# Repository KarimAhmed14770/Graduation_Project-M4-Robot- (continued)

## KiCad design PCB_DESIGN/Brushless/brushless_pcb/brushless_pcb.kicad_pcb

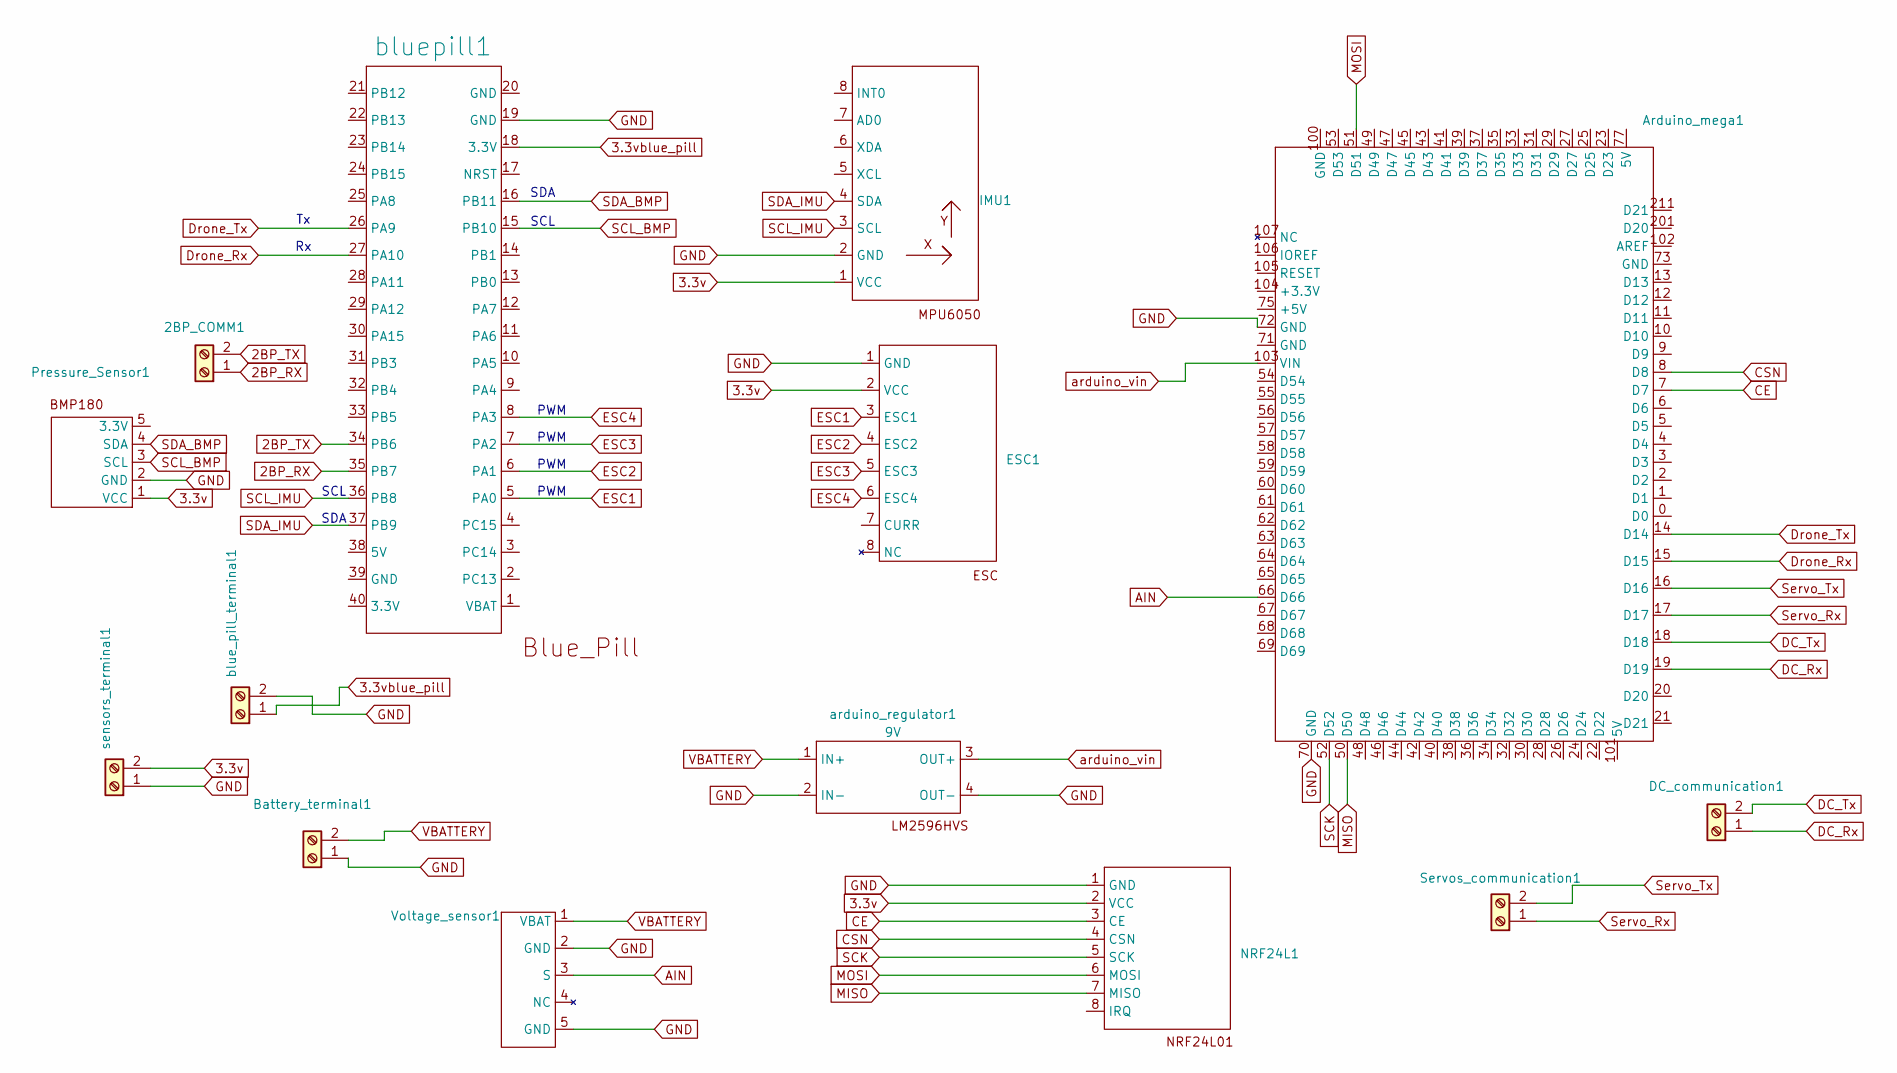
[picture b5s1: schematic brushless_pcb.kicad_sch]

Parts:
2BP_COMM1: TerminalBlock_Altech_AK300-2_P5.00mm
Arduino_mega1: mega_reverse
Battery_terminal1: battery
DC_communication1: TerminalBlock_Altech_AK300-2_P5.00mm
ESC1: TerminalBlock_bornier-8_P5.08mm
IMU1: MPU6050
NRF24L1: NRF24L1
Pressure_Sensor1: BMP180
Servos_communication1: TerminalBlock_Altech_AK300-2_P5.00mm
Voltage_sensor1: Voltage_sensor
arduino_regulator1: 9V; LM2596HVS
blue_pill_terminal1: Screw_Terminal_01x02; TerminalBlock_Altech_AK300-2_P5.00mm
bluepill1: blue_pill
sensors_terminal1: Screw_Terminal_01x02; TerminalBlock_Altech_AK300-2_P5.00mm

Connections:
2BP_RX: 2BP_COMM1.1, bluepill1.35 (PB7)
2BP_TX: 2BP_COMM1.2, bluepill1.34 (PB6)
3.3v: ESC1.2 (VCC), IMU1.1 (VCC), NRF24L1.2 (VCC), Pressure_Sensor1.1 (VCC), sensors_terminal1.2
3.3vblue_pill: blue_pill_terminal1.1, bluepill1.18 (3.3V)
AIN: Arduino_mega1.66 (D66), Voltage_sensor1.3 (S)
CE: Arduino_mega1.7 (D7), NRF24L1.3 (CE)
CSN: Arduino_mega1.8 (D8), NRF24L1.4 (CSN)
DC_Rx: Arduino_mega1.19 (D19), DC_communication1.1
DC_Tx: Arduino_mega1.18 (D18), DC_communication1.2
Drone_Rx: Arduino_mega1.15 (D15), bluepill1.27 (PA10)
Drone_Tx: Arduino_mega1.14 (D14), bluepill1.26 (PA9)
ESC1: ESC1.3 (ESC1), bluepill1.5 (PA0)
ESC2: ESC1.4 (ESC2), bluepill1.6 (PA1)
ESC3: ESC1.5 (ESC3), bluepill1.7 (PA2)
ESC4: ESC1.6 (ESC4), bluepill1.8 (PA3)
GND: Arduino_mega1.70 (GND), Arduino_mega1.72 (GND), Battery_terminal1.1, ESC1.1 (GND), IMU1.2 (GND), NRF24L1.1 (GND), Pressure_Sensor1.2 (GND), Voltage_sensor1.2 (GND), Voltage_sensor1.5 (GND), arduino_regulator1.2 (IN-), arduino_regulator1.4 (OUT-), blue_pill_terminal1.2, bluepill1.19 (GND), sensors_terminal1.1
MISO: Arduino_mega1.50 (D50), NRF24L1.7 (MISO)
MOSI: Arduino_mega1.51 (D51), NRF24L1.6 (MOSI)
SCK: Arduino_mega1.52 (D52), NRF24L1.5 (SCK)
SCL_BMP: Pressure_Sensor1.3 (SCL), bluepill1.15 (PB10)
SCL_IMU: IMU1.3 (SCL), bluepill1.36 (PB8)
SDA_BMP: Pressure_Sensor1.4 (SDA), bluepill1.16 (PB11)
SDA_IMU: IMU1.4 (SDA), bluepill1.37 (PB9)
Servo_Rx: Arduino_mega1.17 (D17), Servos_communication1.1
Servo_Tx: Arduino_mega1.16 (D16), Servos_communication1.2
VBATTERY: Battery_terminal1.2, Voltage_sensor1.1 (VBAT), arduino_regulator1.1 (IN+)
arduino_vin: Arduino_mega1.103 (VIN), arduino_regulator1.3 (OUT+)

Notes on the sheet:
PWM
SDA
SCL
SCL

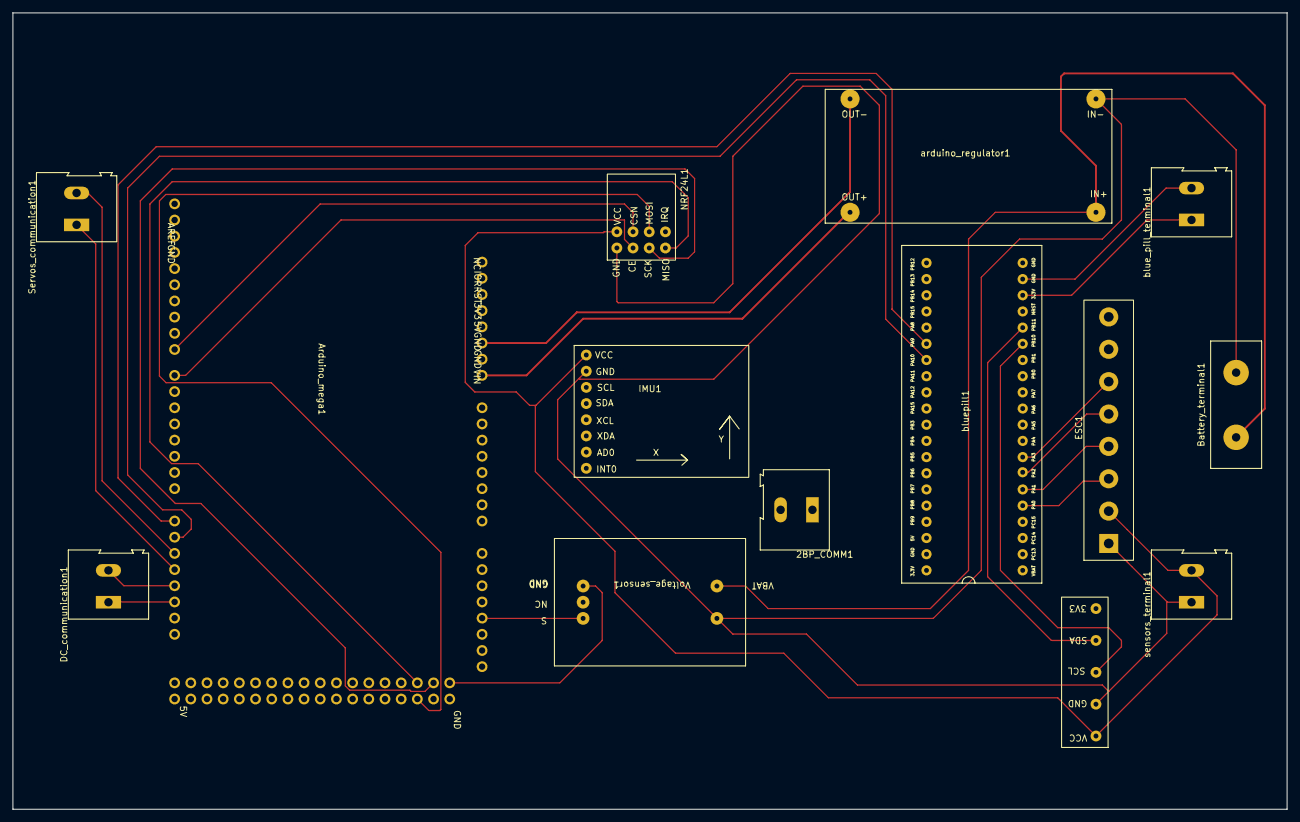
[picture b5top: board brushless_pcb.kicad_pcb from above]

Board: 2 copper layers, 200.0 x 125.0 mm, 14 parts (0 on the bottom side), 27 nets.

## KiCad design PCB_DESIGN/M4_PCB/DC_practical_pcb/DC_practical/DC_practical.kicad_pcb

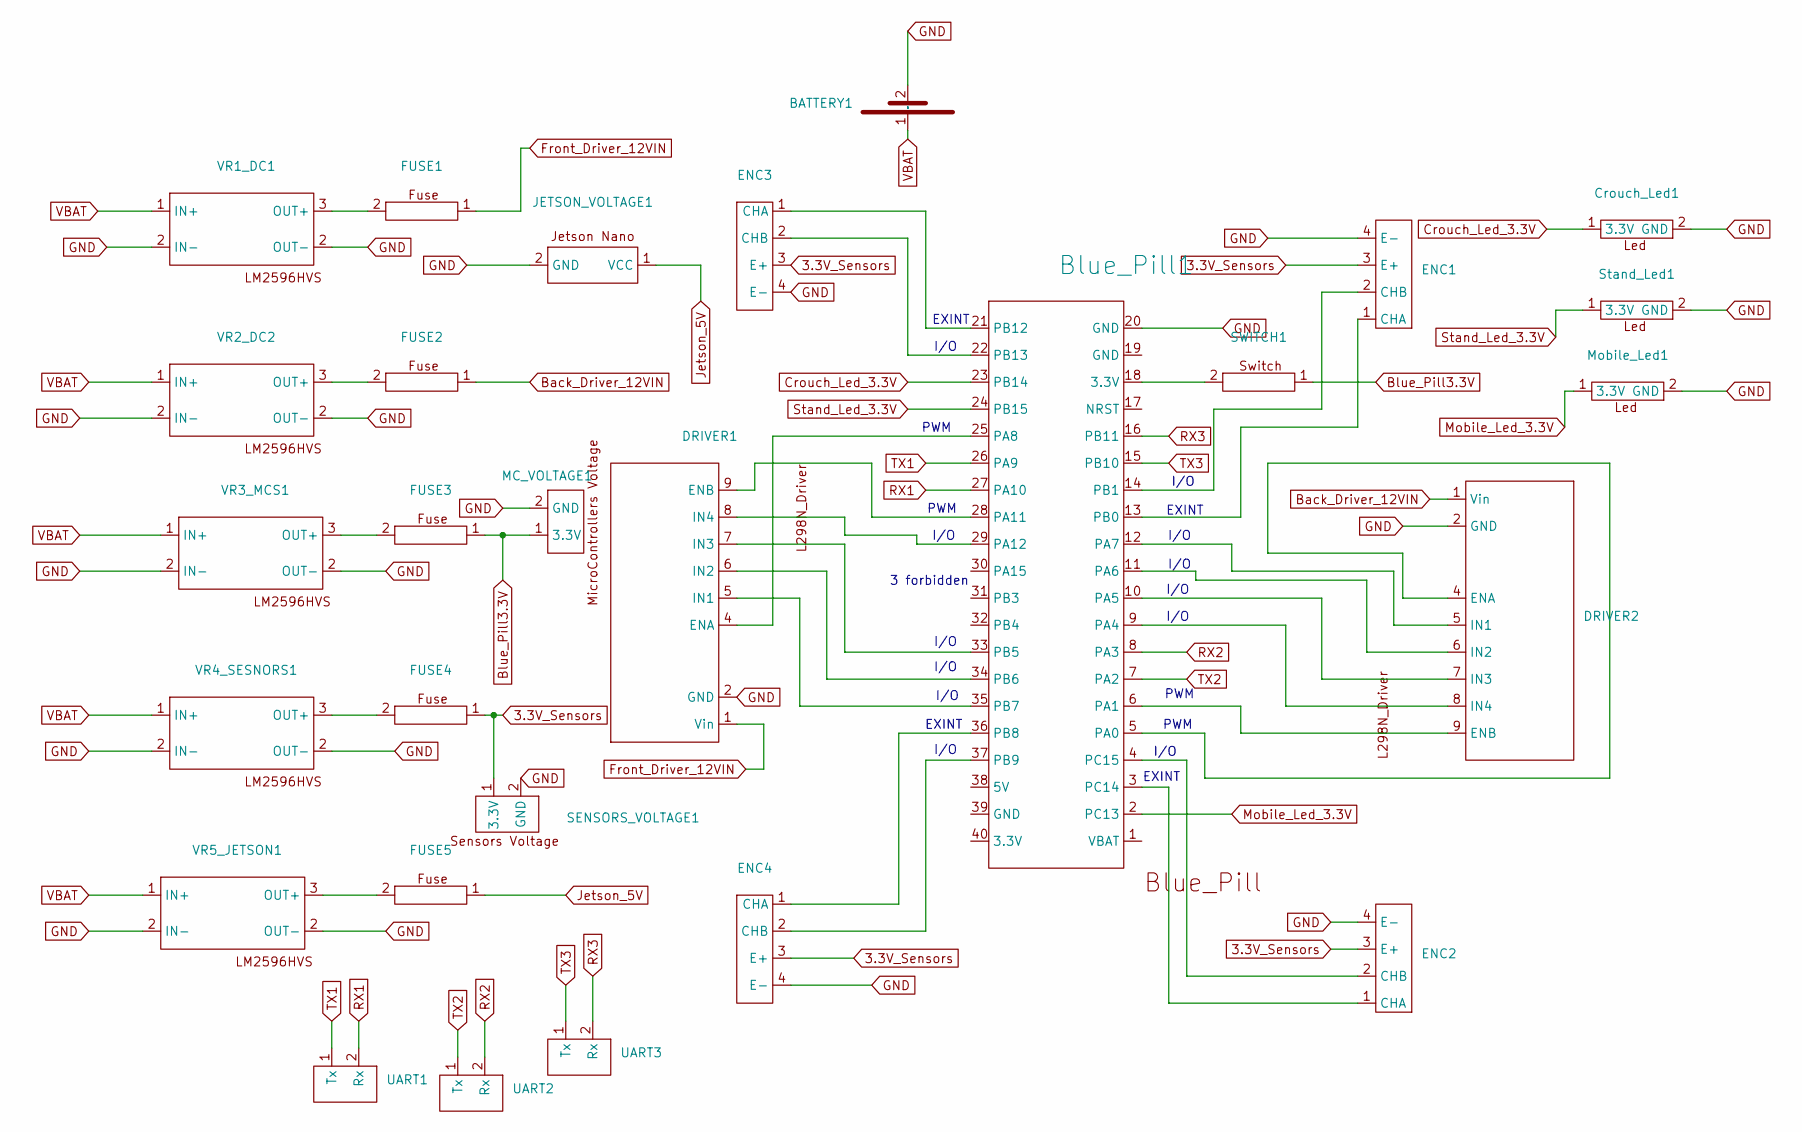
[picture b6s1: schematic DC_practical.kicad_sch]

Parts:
BATTERY1: battery
Blue_Pill1: blue_pill
Crouch_Led1: LED
DRIVER1, DRIVER2: L298N
ENC1, ENC2, ENC3, ENC4: Encoder
FUSE1, FUSE2, FUSE3, FUSE4, FUSE5: Fuse_Holder
JETSON_VOLTAGE1: Jetson_Voltage
MC_VOLTAGE1: Microcontrollers
Mobile_Led1: LED
SENSORS_VOLTAGE1: sensors
SWITCH1: switch
Stand_Led1: LED
UART1, UART2, UART3: communication
VR1_DC1, VR2_DC2, VR3_MCS1, VR4_SESNORS1, VR5_JETSON1: LM2596HVS

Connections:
3.3V_Sensors: ENC1.3 (E+), ENC2.3 (E+), ENC3.3 (E+), ENC4.3 (E+), FUSE4.1, SENSORS_VOLTAGE1.1 (3.3V)
Back_Driver_12VIN: DRIVER2.1 (Vin), FUSE2.1
Blue_Pill3.3V: FUSE3.1, MC_VOLTAGE1.1 (3.3V), SWITCH1.1
Crouch_Led_3.3V: Blue_Pill1.23 (PB14), Crouch_Led1.1 (3.3V)
Front_Driver_12VIN: DRIVER1.1 (Vin), FUSE1.1
GND: BATTERY1.2 (GND), Blue_Pill1.20 (GND), Crouch_Led1.2 (GND), DRIVER1.2 (GND), DRIVER2.2 (GND), ENC1.4 (E-), ENC2.4 (E-), ENC3.4 (E-), ENC4.4 (E-), JETSON_VOLTAGE1.2 (GND), MC_VOLTAGE1.2 (GND), Mobile_Led1.2 (GND), SENSORS_VOLTAGE1.2 (GND), Stand_Led1.2 (GND), VR1_DC1.2 (IN-), VR2_DC2.2 (OUT-), VR3_MCS1.2 (IN-), VR4_SESNORS1.2 (OUT-), VR5_JETSON1.2 (OUT-)
Jetson_5V: FUSE5.1, JETSON_VOLTAGE1.1 (VCC)
Mobile_Led_3.3V: Blue_Pill1.2 (PC13), Mobile_Led1.1 (3.3V)
unnamed: Blue_Pill1.18 (3.3V), SWITCH1.2
unnamed: Blue_Pill1.5 (PA0), DRIVER2.4 (ENA)
unnamed: Blue_Pill1.6 (PA1), DRIVER2.9 (ENB)
unnamed: Blue_Pill1.9 (PA4), DRIVER2.8 (IN4)
unnamed: Blue_Pill1.10 (PA5), DRIVER2.7 (IN3)
unnamed: Blue_Pill1.11 (PA6), DRIVER2.6 (IN2)
unnamed: Blue_Pill1.12 (PA7), DRIVER2.5 (IN1)
unnamed: Blue_Pill1.25 (PA8), DRIVER1.4 (ENA)
unnamed: Blue_Pill1.28 (PA11), DRIVER1.9 (ENB)
unnamed: Blue_Pill1.29 (PA12), DRIVER1.8 (IN4)
unnamed: Blue_Pill1.13 (PB0), ENC1.1 (CHA)
unnamed: Blue_Pill1.14 (PB1), ENC1.2 (CHB)
unnamed: Blue_Pill1.33 (PB5), DRIVER1.7 (IN3)
unnamed: Blue_Pill1.34 (PB6), DRIVER1.6 (IN2)
unnamed: Blue_Pill1.35 (PB7), DRIVER1.5 (IN1)
unnamed: Blue_Pill1.36 (PB8), ENC4.1 (CHA)
unnamed: Blue_Pill1.37 (PB9), ENC4.2 (CHB)
unnamed: Blue_Pill1.21 (PB12), ENC3.1 (CHA)
unnamed: Blue_Pill1.22 (PB13), ENC3.2 (CHB)
unnamed: Blue_Pill1.3 (PC14), ENC2.1 (CHA)
unnamed: Blue_Pill1.4 (PC15), ENC2.2 (CHB)
unnamed: FUSE1.2, VR1_DC1.3 (OUT+)
unnamed: FUSE2.2, VR2_DC2.3 (OUT+)
unnamed: FUSE3.2, VR3_MCS1.3 (OUT+)
unnamed: FUSE4.2, VR4_SESNORS1.3 (OUT+)
unnamed: FUSE5.2, VR5_JETSON1.3 (OUT+)
RX1: Blue_Pill1.27 (PA10), UART1.2 (Rx)
RX2: Blue_Pill1.8 (PA3), UART2.2 (Rx)
RX3: Blue_Pill1.16 (PB11), UART3.2 (Rx)
Stand_Led_3.3V: Blue_Pill1.24 (PB15), Stand_Led1.1 (3.3V)
TX1: Blue_Pill1.26 (PA9), UART1.1 (Tx)
TX2: Blue_Pill1.7 (PA2), UART2.1 (Tx)
TX3: Blue_Pill1.15 (PB10), UART3.1 (Tx)
VBAT: BATTERY1.1 (VDD), VR1_DC1.1 (IN+), VR2_DC2.1 (IN+), VR3_MCS1.1 (IN+), VR4_SESNORS1.1 (IN+), VR5_JETSON1.1 (IN+)

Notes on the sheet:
I/O
PWM
EXINT
3 forbidden

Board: 2 copper layers, 28 parts (0 on the bottom side), 42 nets, no tracks yet.

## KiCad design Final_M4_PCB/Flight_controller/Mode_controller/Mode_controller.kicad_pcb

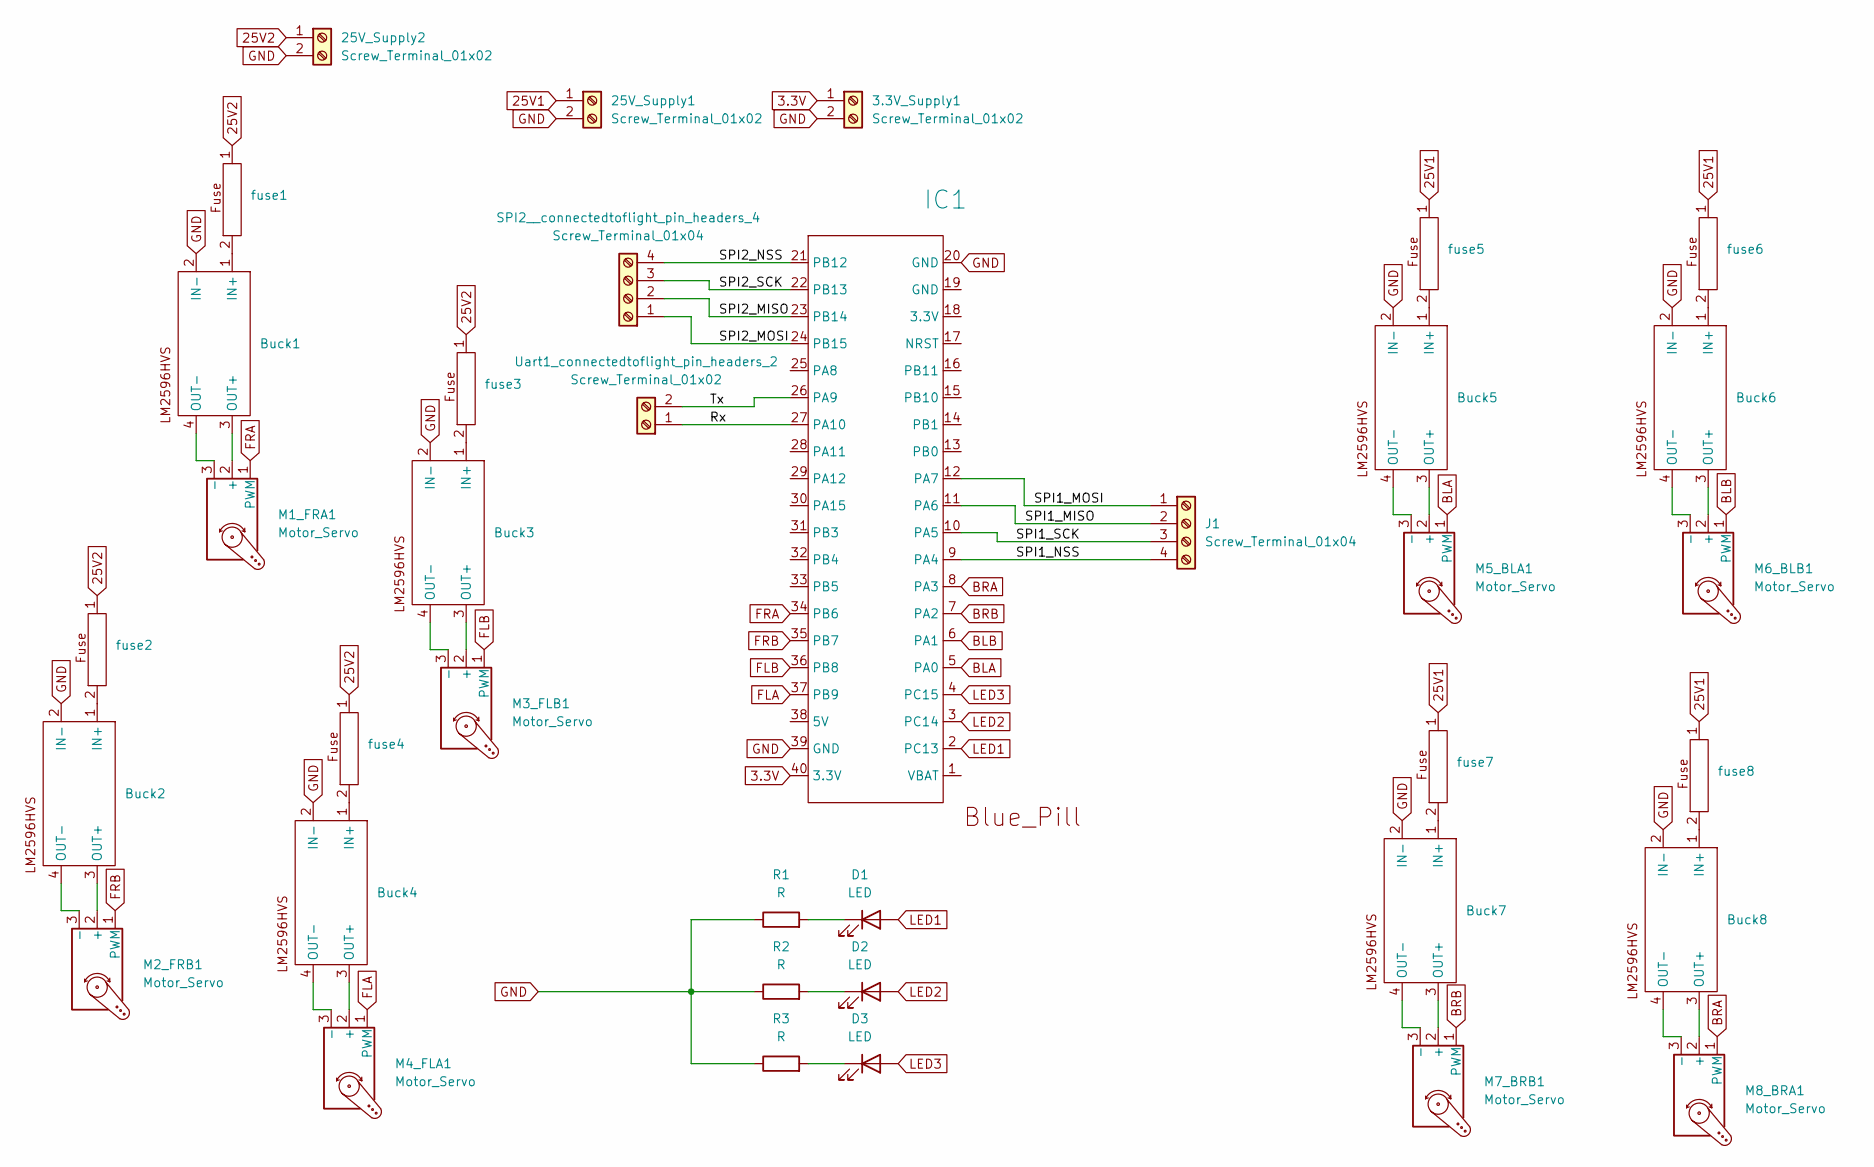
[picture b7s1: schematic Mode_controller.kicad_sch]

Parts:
3.3V_Supply1: Screw_Terminal_01x02; PinHeader_1x02_P2.54mm_Vertical
25V_Supply1, 25V_Supply2: Screw_Terminal_01x02; TerminalBlock_Dinkle_DT-55-B01X-02_P10.00mm
Buck1, Buck2, Buck3, Buck4, Buck5, Buck6, Buck7, Buck8: LM2596HVS
D1, D2, D3: LED; LED_D3.0mm
IC1: blue_pill
J1: Screw_Terminal_01x04; PinHeader_1x04_P2.54mm_Vertical
M1_FRA1, M2_FRB1, M3_FLB1, M4_FLA1, M5_BLA1, M6_BLB1, M7_BRB1, M8_BRA1: Motor_Servo; Servo
R1, R2, R3: R; R_Axial_DIN0204_L3.6mm_D1.6mm_P2.54mm_Vertical
SPI2__connectedtoflight_pin_headers_4: Screw_Terminal_01x04; PinHeader_1x04_P2.54mm_Vertical
Uart1_connectedtoflight_pin_headers_2: Screw_Terminal_01x02; PinHeader_1x02_P2.54mm_Vertical
fuse1, fuse2, fuse3, fuse4, fuse5, fuse6, fuse7, fuse8: Fuse_Holder

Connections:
3.3V: 3.3V_Supply1.1, IC1.40 (3.3V)
25V1: 25V_Supply1.1, fuse5.1, fuse6.1, fuse7.1, fuse8.1
25V2: 25V_Supply2.1, fuse1.1, fuse2.1, fuse3.1, fuse4.1
/Rx: IC1.27 (PA10), Uart1_connectedtoflight_pin_headers_2.1
/SPI1_MISO: IC1.11 (PA6), J1.2
/SPI1_MOSI: IC1.12 (PA7), J1.1
/SPI1_NSS: IC1.9 (PA4), J1.4
/SPI1_SCK: IC1.10 (PA5), J1.3
/SPI2_MISO: IC1.23 (PB14), SPI2__connectedtoflight_pin_headers_4.2
/SPI2_MOSI: IC1.24 (PB15), SPI2__connectedtoflight_pin_headers_4.1
/SPI2_NSS: IC1.21 (PB12), SPI2__connectedtoflight_pin_headers_4.4
/SPI2_SCK: IC1.22 (PB13), SPI2__connectedtoflight_pin_headers_4.3
/Tx: IC1.26 (PA9), Uart1_connectedtoflight_pin_headers_2.2
BLA: IC1.5 (PA0), M5_BLA1.1 (PWM)
BLB: IC1.6 (PA1), M6_BLB1.1 (PWM)
BRA: IC1.8 (PA3), M8_BRA1.1 (PWM)
BRB: IC1.7 (PA2), M7_BRB1.1 (PWM)
FLA: IC1.37 (PB9), M4_FLA1.1 (PWM)
FLB: IC1.36 (PB8), M3_FLB1.1 (PWM)
FRA: IC1.34 (PB6), M1_FRA1.1 (PWM)
FRB: IC1.35 (PB7), M2_FRB1.1 (PWM)
GND: 3.3V_Supply1.2, 25V_Supply1.2, 25V_Supply2.2, Buck1.2 (IN-), Buck2.2 (IN-), Buck3.2 (IN-), Buck4.2 (IN-), Buck5.2 (IN-), Buck6.2 (IN-), Buck7.2 (IN-), Buck8.2 (IN-), IC1.20 (GND), IC1.39 (GND), R1.1, R2.1, R3.1
LED1: D1.2 (A), IC1.2 (PC13)
LED2: D2.2 (A), IC1.3 (PC14)
LED3: D3.2 (A), IC1.4 (PC15)
unnamed: Buck1.1 (IN+), fuse1.2
unnamed: Buck1.3 (OUT+), M1_FRA1.2 (+)
unnamed: Buck1.4 (OUT-), M1_FRA1.3 (-)
unnamed: Buck2.1 (IN+), fuse2.2
unnamed: Buck2.3 (OUT+), M2_FRB1.2 (+)
unnamed: Buck2.4 (OUT-), M2_FRB1.3 (-)
unnamed: Buck3.1 (IN+), fuse3.2
unnamed: Buck3.3 (OUT+), M3_FLB1.2 (+)
unnamed: Buck3.4 (OUT-), M3_FLB1.3 (-)
unnamed: Buck4.1 (IN+), fuse4.2
unnamed: Buck4.3 (OUT+), M4_FLA1.2 (+)
unnamed: Buck4.4 (OUT-), M4_FLA1.3 (-)
unnamed: Buck5.1 (IN+), fuse5.2
unnamed: Buck5.3 (OUT+), M5_BLA1.2 (+)
unnamed: Buck5.4 (OUT-), M5_BLA1.3 (-)
unnamed: Buck6.1 (IN+), fuse6.2
unnamed: Buck6.3 (OUT+), M6_BLB1.2 (+)
unnamed: Buck6.4 (OUT-), M6_BLB1.3 (-)
unnamed: Buck7.1 (IN+), fuse7.2
unnamed: Buck7.3 (OUT+), M7_BRB1.2 (+)
unnamed: Buck7.4 (OUT-), M7_BRB1.3 (-)
unnamed: Buck8.1 (IN+), fuse8.2
unnamed: Buck8.3 (OUT+), M8_BRA1.2 (+)
unnamed: Buck8.4 (OUT-), M8_BRA1.3 (-)
unnamed: D1.1 (K), R1.2
unnamed: D2.1 (K), R2.2
unnamed: D3.1 (K), R3.2

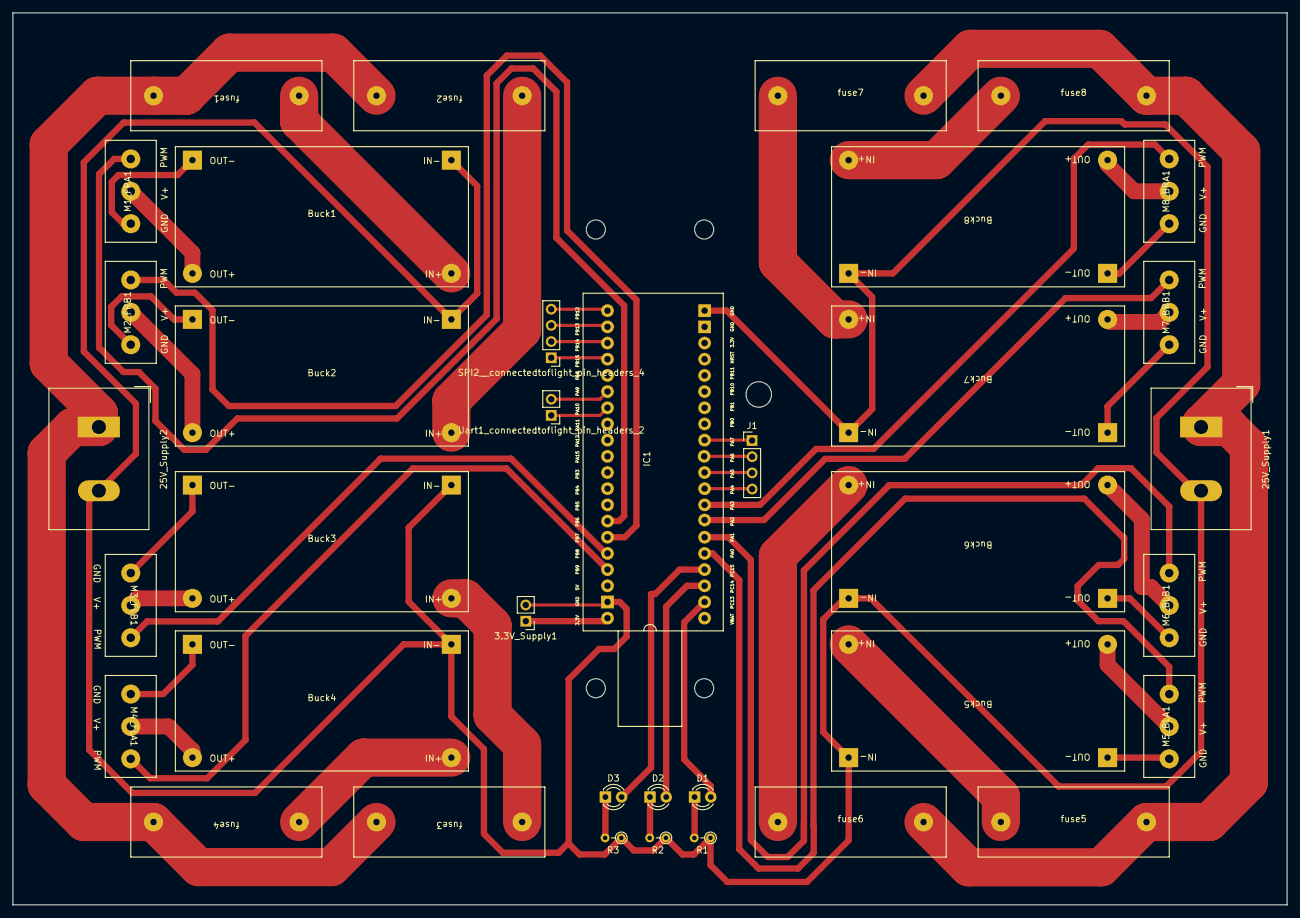
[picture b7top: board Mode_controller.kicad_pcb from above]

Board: 2 copper layers, 200.0 x 140.0 mm, 37 parts (0 on the bottom side), 52 nets.

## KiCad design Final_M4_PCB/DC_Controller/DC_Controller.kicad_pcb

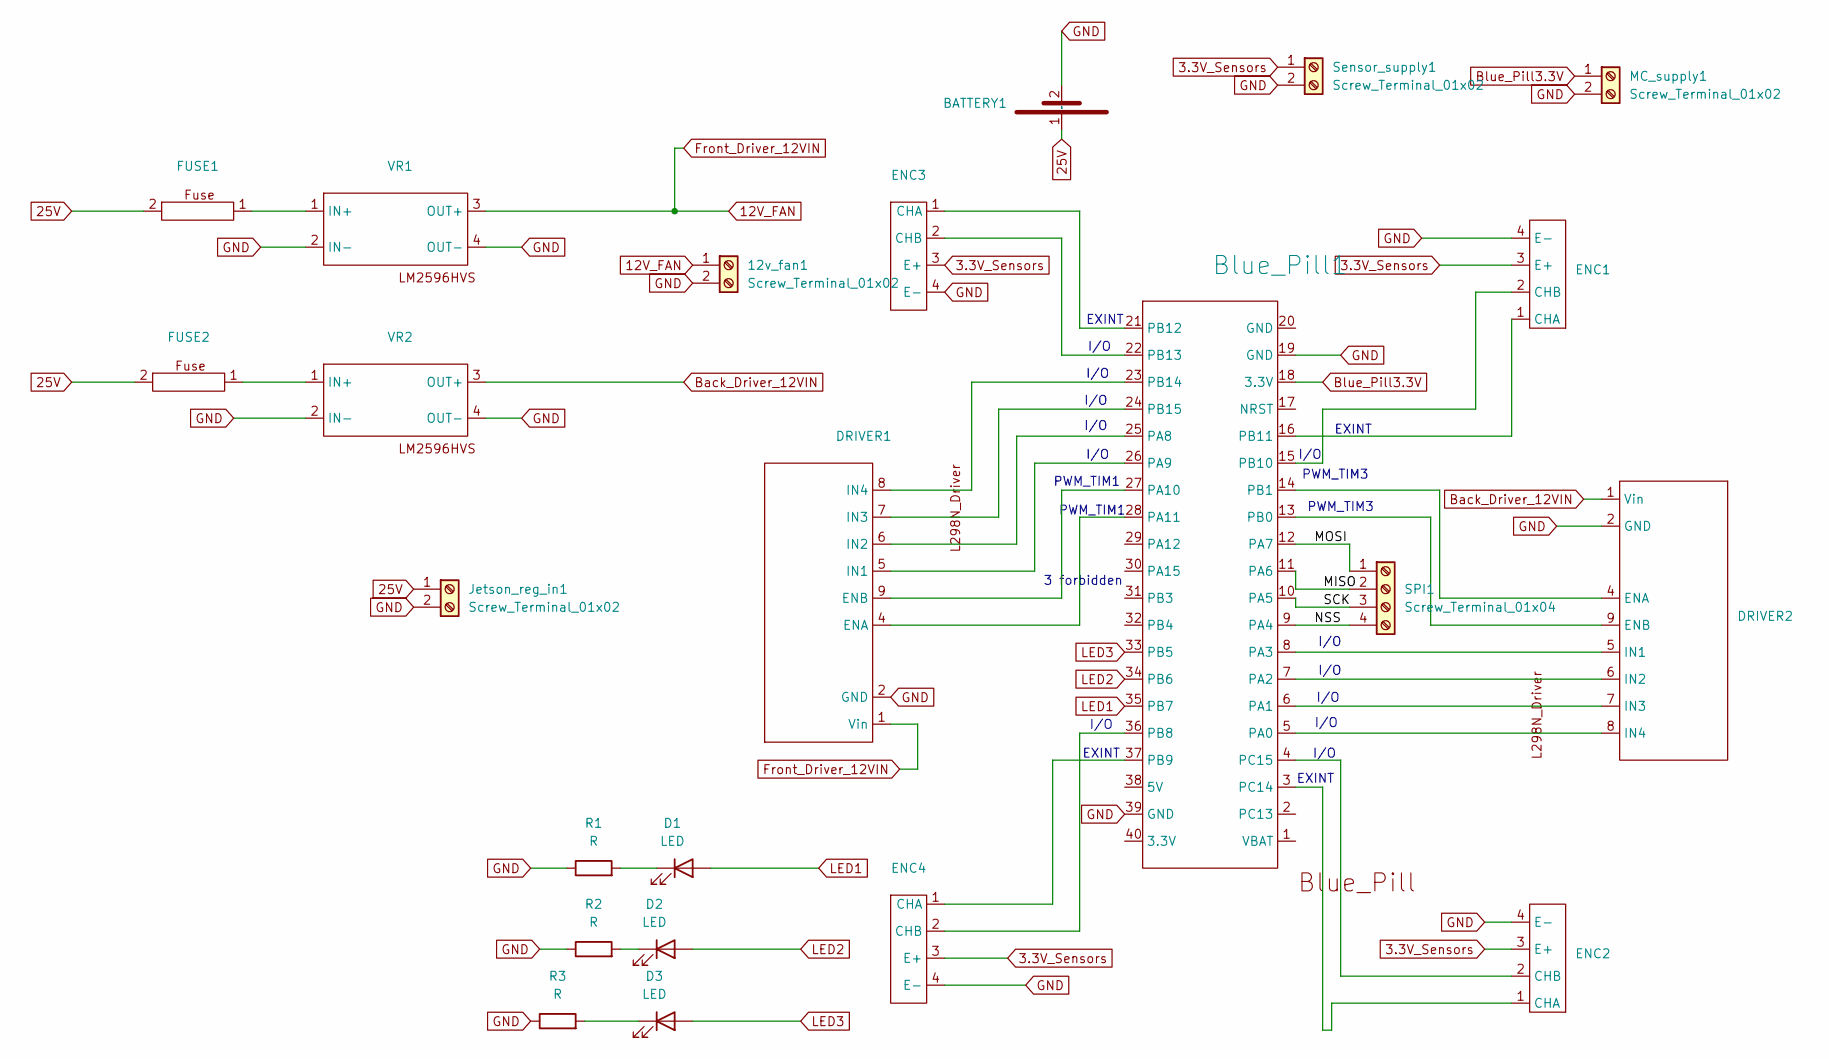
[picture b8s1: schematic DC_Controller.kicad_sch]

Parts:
12v_fan1: Screw_Terminal_01x02; TerminalBlock_bornier-2_P5.08mm
BATTERY1: TerminalBlock_Dinkle_DT-55-B01X-02_P10.00mm
Blue_Pill1: blue_pill
D1, D2, D3: LED; LED_D3.0mm
DRIVER1, DRIVER2: L298N
ENC1, ENC2, ENC3, ENC4: Encoder
FUSE1, FUSE2: Fuse_Holder
Jetson_reg_in1: Screw_Terminal_01x02; PinHeader_1x02_P2.54mm_Vertical
MC_supply1: Screw_Terminal_01x02; PinHeader_1x02_P2.54mm_Vertical
R1, R2, R3: R; R_Axial_DIN0204_L3.6mm_D1.6mm_P2.54mm_Vertical
SPI1: Screw_Terminal_01x04; PinHeader_1x04_P2.54mm_Vertical
Sensor_supply1: Screw_Terminal_01x02; PinHeader_1x02_P2.54mm_Vertical
VR1, VR2: LM2596HVS

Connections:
3.3V_Sensors: ENC1.3 (E+), ENC2.3 (E+), ENC3.3 (E+), ENC4.3 (E+), Sensor_supply1.1
12V_FAN: 12v_fan1.1, DRIVER1.1 (Vin), VR1.3 (OUT+)
25V: BATTERY1.1 (VDD), FUSE1.2, FUSE2.2, Jetson_reg_in1.1
/MISO: Blue_Pill1.11 (PA6), SPI1.2
/MOSI: Blue_Pill1.12 (PA7), SPI1.1
/NSS: Blue_Pill1.9 (PA4), SPI1.4
/SCK: Blue_Pill1.10 (PA5), SPI1.3
Back_Driver_12VIN: DRIVER2.1 (Vin), VR2.3 (OUT+)
Blue_Pill3.3V: Blue_Pill1.18 (3.3V), MC_supply1.1
GND: 12v_fan1.2, BATTERY1.2 (GND), Blue_Pill1.19 (GND), Blue_Pill1.39 (GND), DRIVER1.2 (GND), DRIVER2.2 (GND), ENC1.4 (E-), ENC2.4 (E-), ENC3.4 (E-), ENC4.4 (E-), Jetson_reg_in1.2, MC_supply1.2, R1.1, R2.1, R3.1, Sensor_supply1.2, VR1.2 (IN-), VR1.4 (OUT-), VR2.2 (IN-), VR2.4 (OUT-)
LED1: Blue_Pill1.35 (PB7), D1.2 (A)
LED2: Blue_Pill1.34 (PB6), D2.2 (A)
LED3: Blue_Pill1.33 (PB5), D3.2 (A)
unnamed: Blue_Pill1.5 (PA0), DRIVER2.8 (IN4)
unnamed: Blue_Pill1.6 (PA1), DRIVER2.7 (IN3)
unnamed: Blue_Pill1.7 (PA2), DRIVER2.6 (IN2)
unnamed: Blue_Pill1.8 (PA3), DRIVER2.5 (IN1)
unnamed: Blue_Pill1.25 (PA8), DRIVER1.6 (IN2)
unnamed: Blue_Pill1.26 (PA9), DRIVER1.5 (IN1)
unnamed: Blue_Pill1.27 (PA10), DRIVER1.9 (ENB)
unnamed: Blue_Pill1.28 (PA11), DRIVER1.4 (ENA)
unnamed: Blue_Pill1.13 (PB0), DRIVER2.9 (ENB)
unnamed: Blue_Pill1.14 (PB1), DRIVER2.4 (ENA)
unnamed: Blue_Pill1.36 (PB8), ENC4.2 (CHB)
unnamed: Blue_Pill1.37 (PB9), ENC4.1 (CHA)
unnamed: Blue_Pill1.15 (PB10), ENC1.2 (CHB)
unnamed: Blue_Pill1.16 (PB11), ENC1.1 (CHA)
unnamed: Blue_Pill1.21 (PB12), ENC3.1 (CHA)
unnamed: Blue_Pill1.22 (PB13), ENC3.2 (CHB)
unnamed: Blue_Pill1.23 (PB14), DRIVER1.8 (IN4)
unnamed: Blue_Pill1.24 (PB15), DRIVER1.7 (IN3)
unnamed: Blue_Pill1.3 (PC14), ENC2.1 (CHA)
unnamed: Blue_Pill1.4 (PC15), ENC2.2 (CHB)
unnamed: D1.1 (K), R1.2
unnamed: D2.1 (K), R2.2
unnamed: D3.1 (K), R3.2
unnamed: FUSE1.1, VR1.1 (IN+)
unnamed: FUSE2.1, VR2.1 (IN+)

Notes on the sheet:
I/O
EXINT
3 forbidden
PWM_TIM3
PWM_TIM3
PWM_TIM1

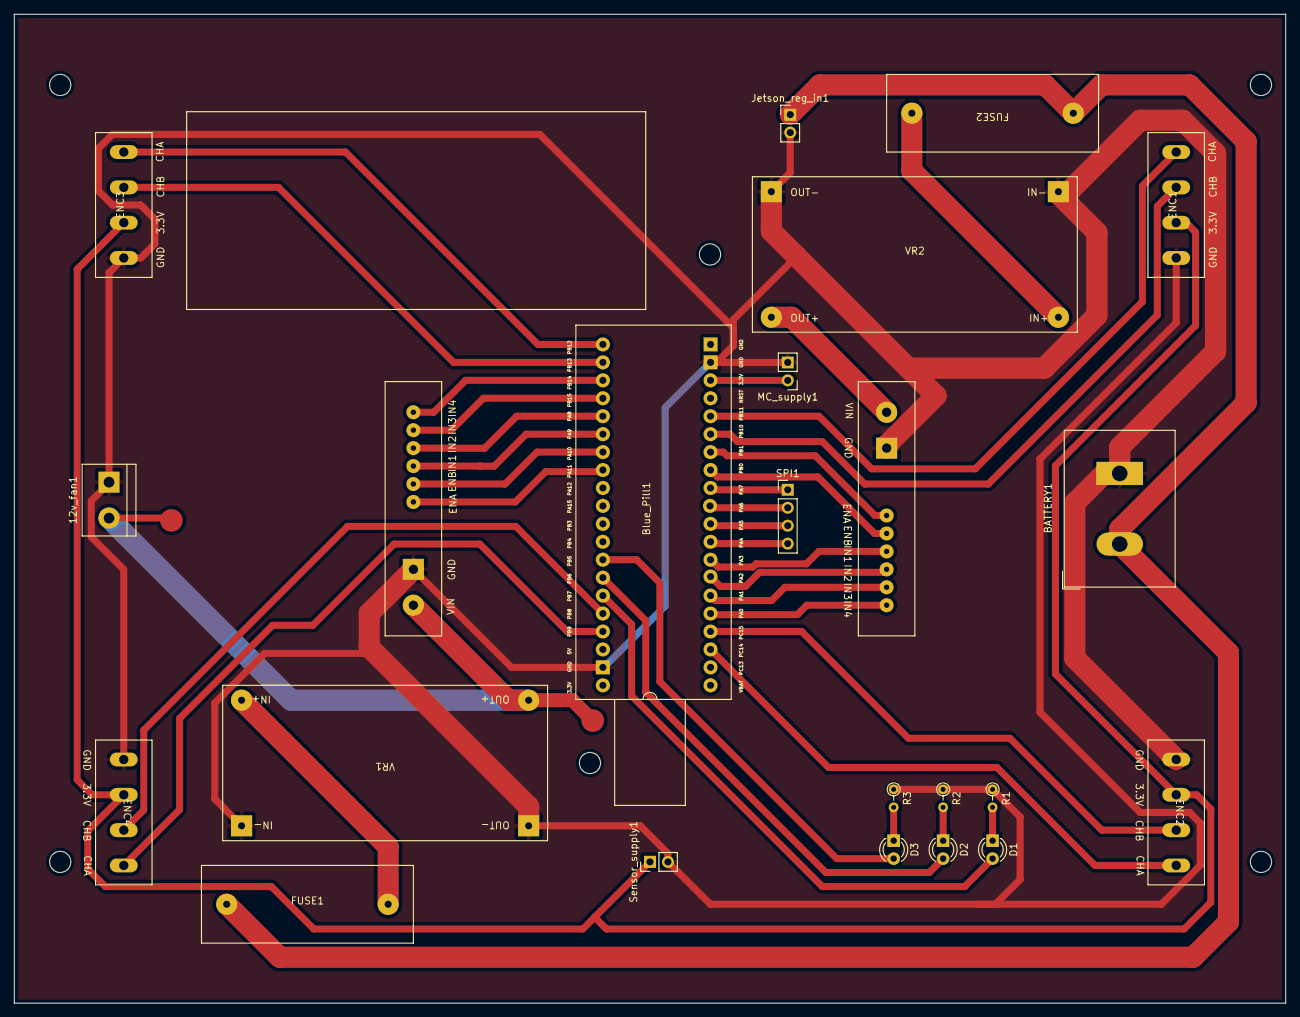
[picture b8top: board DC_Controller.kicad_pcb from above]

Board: 2 copper layers, 180.0 x 140.0 mm, 23 parts (0 on the bottom side), 38 nets.

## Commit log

2025-10-04 Grad_project_files
